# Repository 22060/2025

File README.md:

git clone https://github.com/22060/2025 --recursive

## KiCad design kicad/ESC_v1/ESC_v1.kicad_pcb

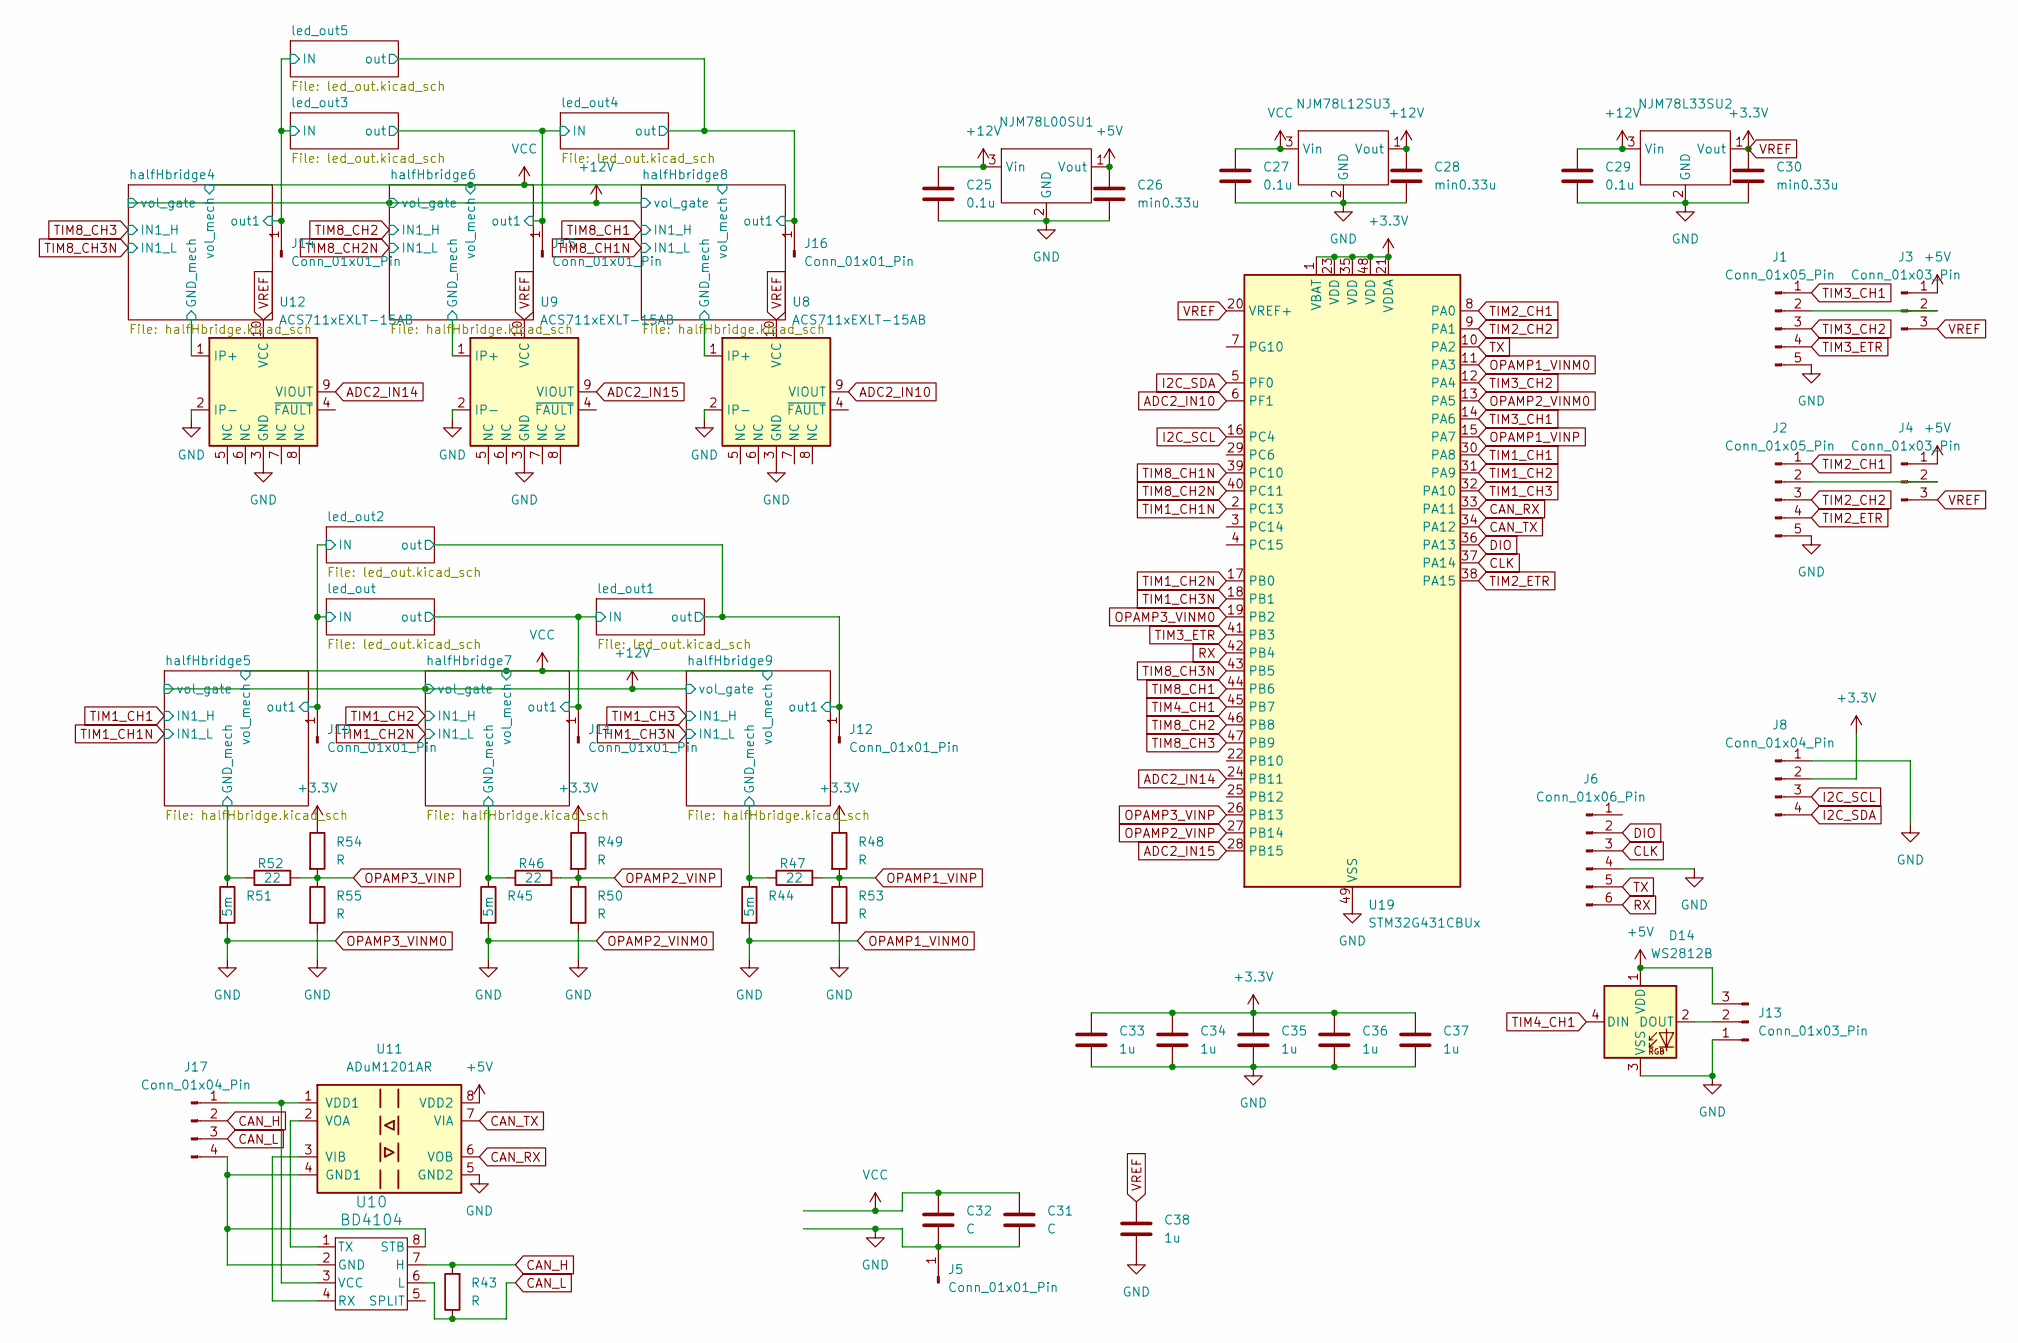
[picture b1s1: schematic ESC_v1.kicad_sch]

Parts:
C25, C27, C29: 0.1u; C_0603_1608Metric
C26, C28, C30: min0.33u; C_0603_1608Metric
C31, C32: C; C_Elec_10x10.2
C33, C34, C35, C36, C37, C38: 1u; C_0603_1608Metric
D14: WS2812B; LED_WS2812B_PLCC4_5.0x5.0mm_P3.2mm
J1, J2: Conn_01x05_Pin; JST_XH_S5B-XH-A_1x05_P2.50mm_Horizontal
J3, J4: Conn_01x03_Pin; PinSocket_1x03_P2.54mm_Vertical
J5: Conn_01x01_Pin; SolderWire-0.75sqmm_1x01_D1.25mm_OD2.3mm
J6: Conn_01x06_Pin; JST_ZH_B6B-ZR_1x06_P1.50mm_Vertical
J8: Conn_01x04_Pin; PinSocket_1x04_P2.54mm_Vertical
J10, J11, J12, J14, J15, J16: Conn_01x01_Pin; TestPoint_Pad_3.0x3.0mm
J13: Conn_01x03_Pin; Molex_KK-254_AE-6410-03A_1x03_P2.54mm_Vertical
J17: Conn_01x04_Pin; JST_PH_S4B-PH-K_1x04_P2.00mm_Horizontal
NJM78L00SU1, NJM78L12SU3, NJM78L33SU2: SOT-89-3
R43, R48, R49, R50, R53, R54, R55: R; R_0603_1608Metric_Pad0.98x0.95mm_HandSolder
R44, R45, R51: 5m; R_2010_5025Metric_Pad1.40x2.65mm_HandSolder
R46, R47, R52: 22; R_0603_1608Metric_Pad0.98x0.95mm_HandSolder
U8, U9, U12: ACS711xEXLT-15AB; Allegro_QFN-12-10-1EP_3x3mm_P0.5mm
U10: BD4104; SOP-J8
U11: ADuM1201AR; SOIC-8_3.9x4.9mm_P1.27mm
U19: STM32G431CBUx; QFN-48-1EP_7x7mm_P0.5mm_EP5.6x5.6mm

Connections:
+5V: C26.1, D14.1 (VDD), J3.1, J4.1, J13.3, NJM78L00SU1.1 (Vout), U11.8 (VDD2)
+12V: C25.1, C28.1, C29.1, NJM78L00SU1.3 (Vin), NJM78L12SU3.1 (Vout), NJM78L33SU2.3 (Vin); also elsewhere on the board
/halfHbridge4/GND_mech: U12.1 (IP+); also elsewhere on the board
/halfHbridge4/out1: J14.1; also elsewhere on the board
/halfHbridge5/GND_mech: R51.1, R52.1; also elsewhere on the board
/halfHbridge5/out1: J10.1; also elsewhere on the board
/halfHbridge6/GND_mech: U9.1 (IP+); also elsewhere on the board
/halfHbridge6/out1: J15.1; also elsewhere on the board
/halfHbridge7/GND_mech: R45.1, R46.1; also elsewhere on the board
/halfHbridge7/out1: J11.1; also elsewhere on the board
/halfHbridge8/GND_mech: U8.1 (IP+); also elsewhere on the board
/halfHbridge8/out1: J16.1; also elsewhere on the board
/halfHbridge9/GND_mech: R44.1, R47.1; also elsewhere on the board
/halfHbridge9/out1: J12.1; also elsewhere on the board
ADC2_IN10: U8.9 (VIOUT), U19.6 (PF1)
ADC2_IN14: U12.9 (VIOUT), U19.24 (PB11)
ADC2_IN15: U9.9 (VIOUT), U19.28 (PB15)
CAN_H: J17.2, R43.2, U10.7 (H)
CAN_L: J17.3, R43.1, U10.6 (L)
CAN_RX: U11.6 (VOB), U19.33 (PA11)
CAN_TX: U11.7 (VIA), U19.34 (PA12)
CLK: J6.3, U19.37 (PA14)
DIO: J6.2, U19.36 (PA13)
I2C_SCL: J8.3, U19.16 (PC4)
I2C_SDA: J8.4, U19.5 (PF0)
unnamed: D14.2 (DOUT), J13.2
unnamed: J1.2, J3.2
unnamed: J2.2, J4.2
unnamed: J17.1, U10.3 (VCC), U11.1 (VDD1)
unnamed: J17.4, U10.2 (GND), U10.8 (STB), U11.4 (GND1)
unnamed: U10.4 (RX), U11.3 (VIB)
unnamed: U10.1 (TX), U11.2 (VOA)
OPAMP1_VINM0: C25.2, C26.2, C27.2, C28.2, C29.2, C30.2, C31.2, C32.2, C33.2, C34.2, C35.2, C36.2, C37.2, C38.2, D14.3 (VSS), J1.5, J2.5, J5.1, J6.4, J8.1, J13.1, NJM78L00SU1.2 (GND), NJM78L12SU3.2 (GND), NJM78L33SU2.2 (GND), R44.2, R45.2, R50.2, R51.2, R53.2, R55.2, U8.2 (IP-), U8.3 (GND), U9.2 (IP-), U9.3 (GND), U11.5 (GND2), U12.2 (IP-), U12.3 (GND), U19.11 (PA3), U19.13 (PA5), U19.19 (PB2), U19.49 (VSS); also elsewhere on the board
OPAMP1_VINP: R47.2, R48.2, R53.1, U19.15 (PA7)
OPAMP2_VINP: R46.2, R49.2, R50.1, U19.27 (PB14)
OPAMP3_VINP: R52.2, R54.2, R55.1, U19.26 (PB13)
RX: J6.6, U19.42 (PB4)
TIM1_CH1: U19.30 (PA8); also elsewhere on the board
TIM1_CH1N: U19.2 (PC13); also elsewhere on the board
TIM1_CH2: U19.31 (PA9); also elsewhere on the board
TIM1_CH2N: U19.17 (PB0); also elsewhere on the board
TIM1_CH3: U19.32 (PA10); also elsewhere on the board
TIM1_CH3N: U19.18 (PB1); also elsewhere on the board
TIM2_CH1: J2.1, U19.8 (PA0)
TIM2_CH2: J2.3, U19.9 (PA1)
TIM2_ETR: J2.4, U19.38 (PA15)
TIM3_CH1: J1.1, U19.14 (PA6)
TIM3_CH2: J1.3, U19.12 (PA4)
TIM3_ETR: J1.4, U19.41 (PB3)
TIM4_CH1: D14.4 (DIN), U19.45 (PB7)
TIM8_CH1: U19.44 (PB6); also elsewhere on the board
TIM8_CH1N: U19.39 (PC10); also elsewhere on the board
TIM8_CH2: U19.46 (PB8); also elsewhere on the board
TIM8_CH2N: U19.40 (PC11); also elsewhere on the board
TIM8_CH3: U19.47 (PB9); also elsewhere on the board
TIM8_CH3N: U19.43 (PB5); also elsewhere on the board
TX: J6.5, U19.10 (PA2)
VCC: C27.1, C31.1, C32.1, NJM78L12SU3.3 (Vin); also elsewhere on the board
VREF: C30.1, C33.1, C34.1, C35.1, C36.1, C37.1, C38.1, J3.3, J4.3, J8.2, NJM78L33SU2.1 (Vout), R48.1, R49.1, R54.1, U8.10 (VCC), U9.10 (VCC), U12.10 (VCC), U19.1 (VBAT), U19.20 (VREF+), U19.21 (VDDA), U19.23 (VDD), U19.35 (VDD), U19.48 (VDD)

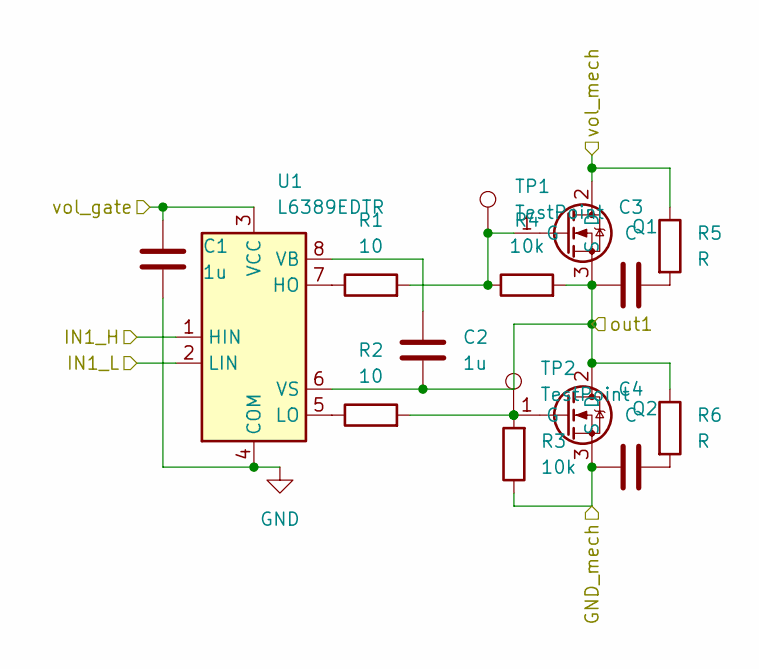
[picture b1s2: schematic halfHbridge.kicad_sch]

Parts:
C1, C2: 1u; C_0603_1608Metric
C3, C4: C; C_0603_1608Metric
Q1, Q2: RD3L07BBG
R1, R2: 10; R_0603_1608Metric_Pad0.98x0.95mm_HandSolder
R3, R4: 10k; R_0603_1608Metric_Pad0.98x0.95mm_HandSolder
R5, R6: R; R_0603_1608Metric_Pad0.98x0.95mm_HandSolder
TP1, TP2: TestPoint; TestPoint_THTPad_D1.5mm_Drill0.7mm
U1: L6389EDTR; SOIC-8_3.9x4.9mm_P1.27mm

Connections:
+12V: C1.1, U1.3 (VCC); also elsewhere on the board
/halfHbridge5/GND_mech: Q2.3 (S), R3.1; also elsewhere on the board
/halfHbridge5/out1: C2.2, Q1.3 (S), Q2.2 (D), R4.2, U1.6 (VS); also elsewhere on the board
unnamed: C3.2, R5.2
unnamed: C4.2, R6.2
unnamed: Q1.1 (G), R1.2, R4.1
unnamed: Q2.1 (G), R2.2, R3.2
unnamed: R1.1, U1.7 (HO)
unnamed: R2.1, U1.5 (LO)
unnamed: C2.1, U1.8 (VB)
OPAMP1_VINM0: C1.2, U1.4 (COM); also elsewhere on the board
TIM1_CH1: U1.1 (HIN); also elsewhere on the board
TIM1_CH1N: U1.2 (LIN); also elsewhere on the board
VCC: Q1.2 (D), R5.1; also elsewhere on the board

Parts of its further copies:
C5, C6, C9, C10, C11, C12, C17, C18, C21, C22: 1u; C_0603_1608Metric
Q3, Q4, Q5, Q6, Q7, Q8, Q9, Q10, Q11, Q12: RD3L07BBG
R7, R8, R13, R14, R15, R16, R25, R26, R31, R32: 10; R_0603_1608Metric_Pad0.98x0.95mm_HandSolder
R9, R10, R17, R18, R19, R20, R27, R28, R33, R34: 10k; R_0603_1608Metric_Pad0.98x0.95mm_HandSolder
U2, U3, U4, U5, U6: L6389EDTR; SOIC-8_3.9x4.9mm_P1.27mm

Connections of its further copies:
+12V: C5.1, C9.1, C10.1, C17.1, C21.1, U2.3 (VCC), U3.3 (VCC), U4.3 (VCC), U5.3 (VCC), U6.3 (VCC); also elsewhere on the board
/halfHbridge4/GND_mech: Q4.3 (S), R9.1; also elsewhere on the board
/halfHbridge4/out1: C6.2, Q3.3 (S), Q4.2 (D), R10.2, U2.6 (VS); also elsewhere on the board
/halfHbridge6/GND_mech: Q8.3 (S), R18.1; also elsewhere on the board
/halfHbridge6/out1: C12.2, Q7.3 (S), Q8.2 (D), R20.2, U4.6 (VS); also elsewhere on the board
/halfHbridge7/GND_mech: Q6.3 (S), R17.1; also elsewhere on the board
/halfHbridge7/out1: C11.2, Q5.3 (S), Q6.2 (D), R19.2, U3.6 (VS); also elsewhere on the board
/halfHbridge8/GND_mech: Q10.3 (S), R27.1; also elsewhere on the board
/halfHbridge8/out1: C18.2, Q9.3 (S), Q10.2 (D), R28.2, U5.6 (VS); also elsewhere on the board
/halfHbridge9/GND_mech: Q12.3 (S), R33.1; also elsewhere on the board
/halfHbridge9/out1: C22.2, Q11.3 (S), Q12.2 (D), R34.2, U6.6 (VS); also elsewhere on the board
unnamed: Q3.1 (G), R7.2, R10.1
unnamed: Q4.1 (G), R8.2, R9.2
unnamed: Q5.1 (G), R13.2, R19.1
unnamed: Q6.1 (G), R14.2, R17.2
unnamed: Q7.1 (G), R15.2, R20.1
unnamed: Q8.1 (G), R16.2, R18.2
unnamed: Q9.1 (G), R25.2, R28.1
unnamed: Q10.1 (G), R26.2, R27.2
unnamed: Q11.1 (G), R31.2, R34.1
unnamed: Q12.1 (G), R32.2, R33.2
unnamed: R7.1, U2.7 (HO)
unnamed: R8.1, U2.5 (LO)
unnamed: C6.1, U2.8 (VB)
unnamed: R13.1, U3.7 (HO)
unnamed: R14.1, U3.5 (LO)
unnamed: C11.1, U3.8 (VB)
unnamed: R15.1, U4.7 (HO)
unnamed: R16.1, U4.5 (LO)
unnamed: C12.1, U4.8 (VB)
unnamed: R25.1, U5.7 (HO)
unnamed: R26.1, U5.5 (LO)
unnamed: C18.1, U5.8 (VB)
unnamed: R31.1, U6.7 (HO)
unnamed: R32.1, U6.5 (LO)
unnamed: C22.1, U6.8 (VB)
OPAMP1_VINM0: C5.2, C9.2, C10.2, C17.2, C21.2, U2.4 (COM), U3.4 (COM), U4.4 (COM), U5.4 (COM), U6.4 (COM); also elsewhere on the board
TIM1_CH2: U3.1 (HIN); also elsewhere on the board
TIM1_CH2N: U3.2 (LIN); also elsewhere on the board
TIM1_CH3: U6.1 (HIN); also elsewhere on the board
TIM1_CH3N: U6.2 (LIN); also elsewhere on the board
TIM8_CH1: U5.1 (HIN); also elsewhere on the board
TIM8_CH1N: U5.2 (LIN); also elsewhere on the board
TIM8_CH2: U4.1 (HIN); also elsewhere on the board
TIM8_CH2N: U4.2 (LIN); also elsewhere on the board
TIM8_CH3: U2.1 (HIN); also elsewhere on the board
TIM8_CH3N: U2.2 (LIN); also elsewhere on the board
VCC: Q3.2 (D), Q5.2 (D), Q7.2 (D), Q9.2 (D), Q11.2 (D); also elsewhere on the board

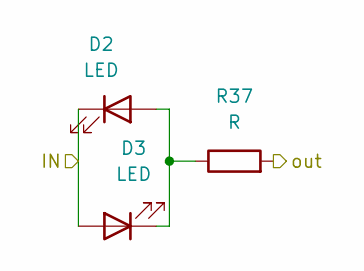
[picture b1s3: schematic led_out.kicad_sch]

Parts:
D2, D3: LED; LED_0603_1608Metric
R37: R; R_0603_1608Metric_Pad0.98x0.95mm_HandSolder

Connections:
/halfHbridge5/out1: D2.1 (K), D3.2 (A); also elsewhere on the board
/halfHbridge7/out1: R37.2; also elsewhere on the board
unnamed: D2.2 (A), D3.1 (K), R37.1

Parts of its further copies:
D1, D4, D5, D6, D7, D8, D9, D10, D11, D12: LED; LED_0603_1608Metric
R38, R39, R40, R41, R42: R; R_0603_1608Metric_Pad0.98x0.95mm_HandSolder

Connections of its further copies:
/halfHbridge4/out1: D1.1 (K), D8.2 (A), D11.1 (K), D12.2 (A); also elsewhere on the board
/halfHbridge5/out1: D6.1 (K), D7.2 (A); also elsewhere on the board
/halfHbridge6/out1: D9.1 (K), D10.2 (A), R40.2; also elsewhere on the board
/halfHbridge7/out1: D4.1 (K), D5.2 (A); also elsewhere on the board
/halfHbridge8/out1: R41.2, R42.2; also elsewhere on the board
/halfHbridge9/out1: R38.2, R39.2; also elsewhere on the board
unnamed: D1.2 (A), D8.1 (K), R40.1
unnamed: D4.2 (A), D5.1 (K), R38.1
unnamed: D6.2 (A), D7.1 (K), R39.1
unnamed: D9.2 (A), D10.1 (K), R41.1
unnamed: D11.2 (A), D12.1 (K), R42.1

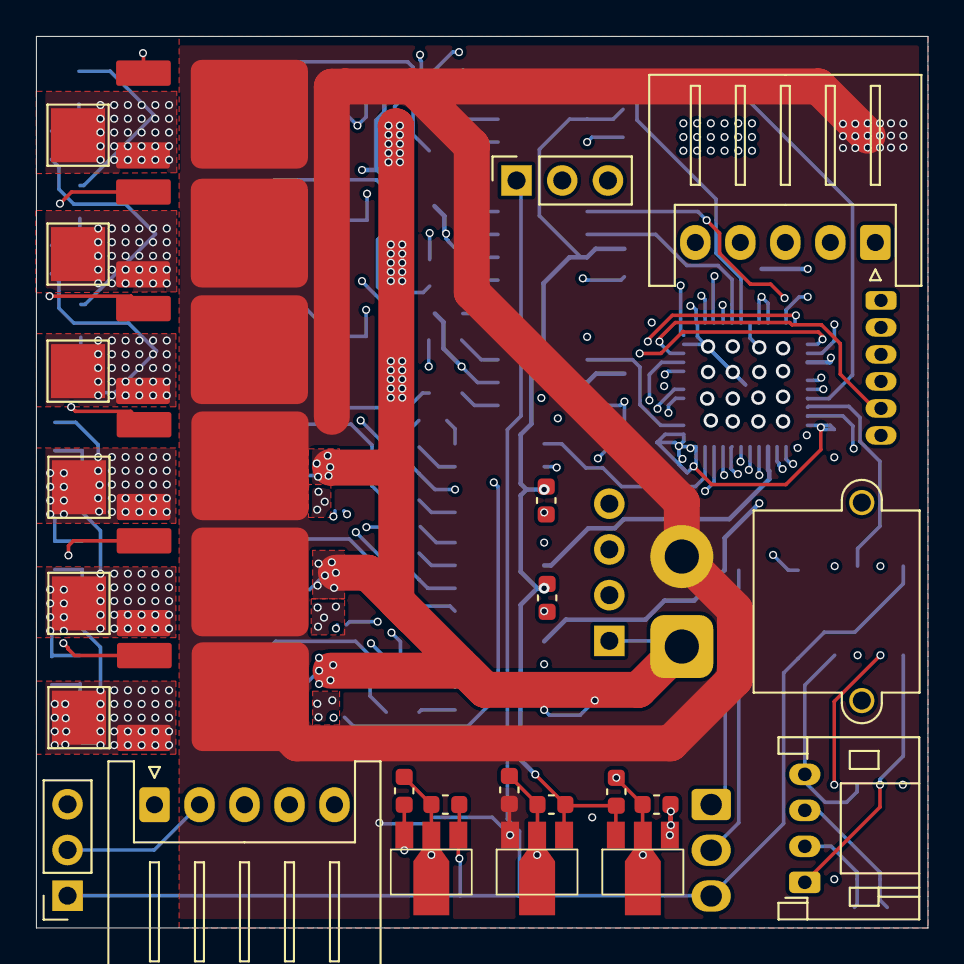
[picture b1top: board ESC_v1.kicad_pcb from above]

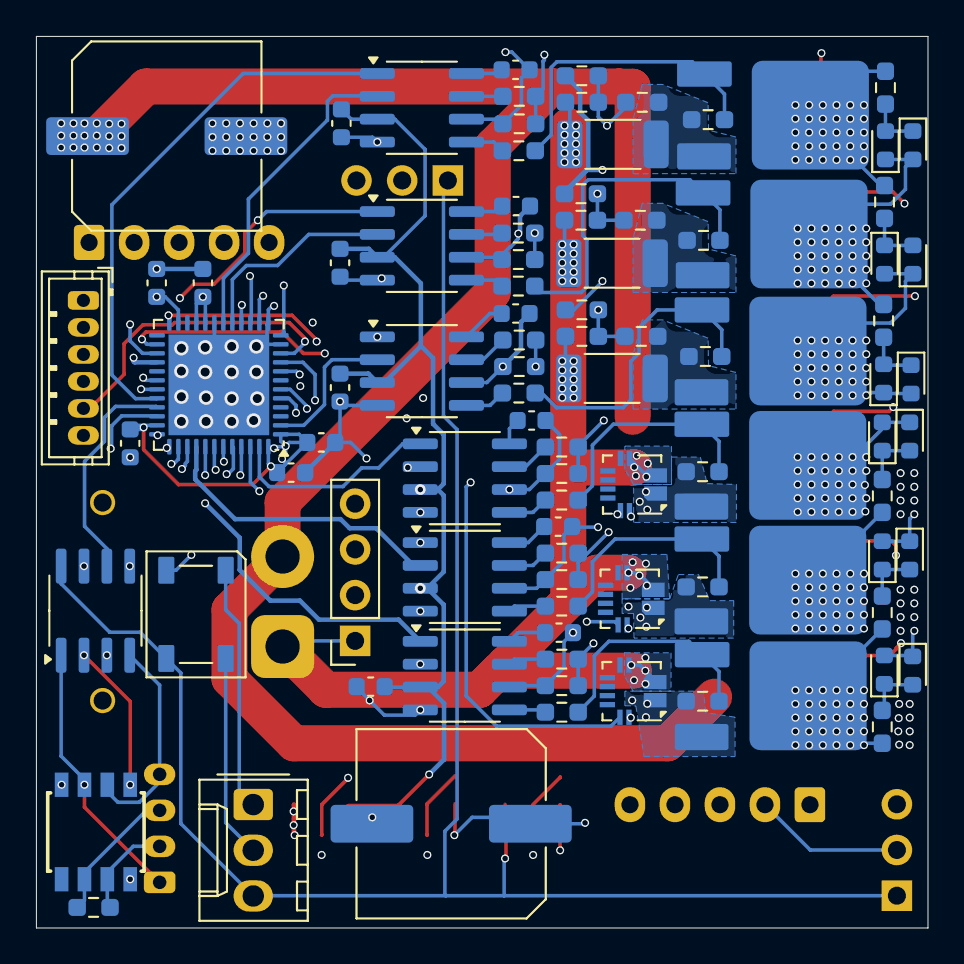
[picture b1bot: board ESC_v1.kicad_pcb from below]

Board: 4 copper layers, 49.5 x 49.5 mm, 123 parts (94 on the bottom side), 95 nets.

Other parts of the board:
J9: Conn_01x02_Pin; AMASS_XT30PW-M_1x02_P2.50mm_Horizontal

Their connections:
OPAMP1_VINM0: J9.1; also elsewhere on the board
VCC: J9.2; also elsewhere on the board

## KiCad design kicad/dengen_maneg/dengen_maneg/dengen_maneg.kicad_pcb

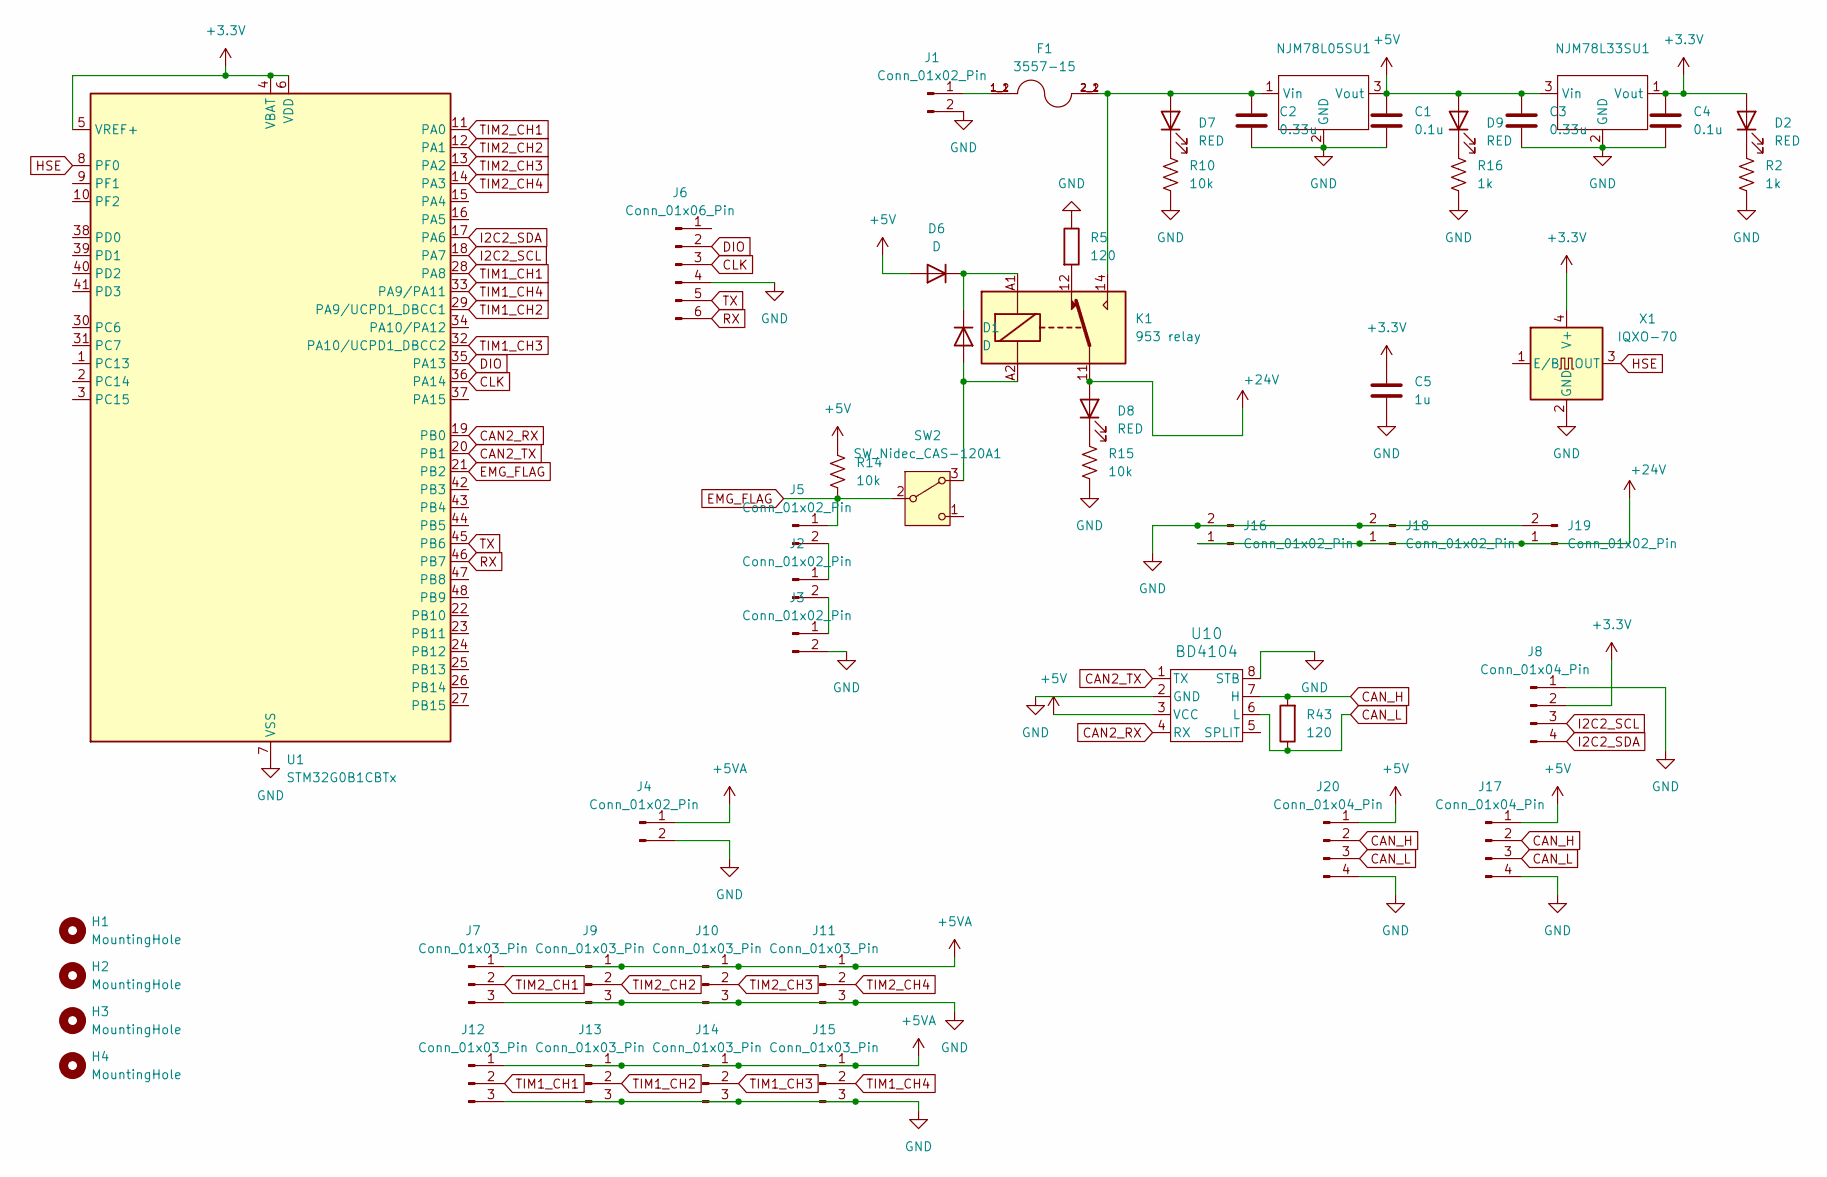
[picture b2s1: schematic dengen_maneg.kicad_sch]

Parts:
C1, C4: 0.1u; C_0603_1608Metric
C2, C3: 0.33u; C_0603_1608Metric
C5: 1u; C_0603_1608Metric
D1, D6: D; D_MicroSMP_AK
D2, D7, D8, D9: RED; LED_0603_1608Metric_Pad1.05x0.95mm_HandSolder
F1: 3557-15; PARTREV D
H1, H2, H3, H4: MountingHole; MountingHole_3.2mm_M3
J1: Conn_01x02_Pin; AMASS_XT60PW-M_1x02_P7.20mm_Horizontal
J2, J3, J5: Conn_01x02_Pin; JST_XH_S2B-XH-A_1x02_P2.50mm_Horizontal
J4: Conn_01x02_Pin; JST_XH_B2B-XH-A_1x02_P2.50mm_Vertical
J6: Conn_01x06_Pin; JST_ZH_B6B-ZR_1x06_P1.50mm_Vertical
J7, J9, J10, J11, J12, J13, J14, J15: Conn_01x03_Pin; JST_XH_B3B-XH-A_1x03_P2.50mm_Vertical
J8: Conn_01x04_Pin; PinSocket_1x04_P2.54mm_Vertical
J16, J18, J19: Conn_01x02_Pin; AMASS_XT30UPB-F_1x02_P5.0mm_Vertical
J17, J20: Conn_01x04_Pin; JST_PH_S4B-PH-K_1x04_P2.00mm_Horizontal
K1: 953 relay
NJM78L05SU1: TO-252-2
NJM78L33SU1: SOT-89-3
R2, R16: 1k; R_0603_1608Metric_Pad0.98x0.95mm_HandSolder
R5: 120; R_Axial_DIN0617_L17.0mm_D6.0mm_P5.08mm_Vertical
R10, R14, R15: 10k; R_0603_1608Metric_Pad0.98x0.95mm_HandSolder
R43: 120; R_0603_1608Metric_Pad0.98x0.95mm_HandSolder
SW2: SW_Nidec_CAS-120A1; JST_XH_B3B-XH-A_1x03_P2.50mm_Vertical
U1: STM32G0B1CBTx; LQFP-48_7x7mm_P0.5mm
U10: BD4104; SOP-J8
X1: IQXO-70; Oscillator_SMD_IQD_IQXO70-4Pin_7.5x5.0mm

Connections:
+3.3V: C4.1, C5.1, D2.2 (A), J8.2, NJM78L33SU1.1 (Vout), U1.4 (VBAT), U1.5 (VREF+), U1.6 (VDD), X1.4 (V+)
+5V: C1.1, C3.1, D6.2 (A), D9.2 (A), J17.1, J20.1, NJM78L05SU1.3 (Vout), NJM78L33SU1.3 (Vin), R14.2, U10.3 (VCC)
+5VA: J4.1, J7.1, J9.1, J10.1, J11.1, J12.1, J13.1, J14.1, J15.1
+24V: D8.2 (A), J16.1, J18.1, J19.1, K1.11
CAN2_RX: U1.19 (PB0), U10.4 (RX)
CAN2_TX: U1.20 (PB1), U10.1 (TX)
CAN_H: J17.2, J20.2, R43.2, U10.7 (H)
CAN_L: J17.3, J20.3, R43.1, U10.6 (L)
CLK: J6.3, U1.36 (PA14)
DIO: J6.2, U1.35 (PA13)
EMG_FLAG: J5.1, R14.1, SW2.2 (B), U1.21 (PB2)
GND: C1.2, C2.2, C3.2, C4.2, C5.2, J1.2, J3.2, J4.2, J6.4, J7.3, J8.1, J9.3, J10.3, J11.3, J12.3, J13.3, J14.3, J15.3, J16.2, J17.4, J18.2, J19.2, J20.4, NJM78L05SU1.2 (GND), NJM78L33SU1.2 (GND), R2.2, R5.1, R10.2, R15.2, R16.2, U1.7 (VSS), U10.2 (GND), U10.8 (STB), X1.2 (GND)
HSE: U1.8 (PF0), X1.3 (OUT)
I2C2_SCL: J8.3, U1.18 (PA7)
I2C2_SDA: J8.4, U1.17 (PA6)
unnamed: D1.2 (A), K1.A2, SW2.3 (A)
unnamed: D1.1 (K), D6.1 (K), K1.A1
unnamed: D2.1 (K), R2.1
unnamed: C2.1, D7.2 (A), F1.2_1, F1.2_2, K1.14, NJM78L05SU1.1 (Vin)
unnamed: D7.1 (K), R10.1
unnamed: D8.1 (K), R15.1
unnamed: D9.1 (K), R16.1
unnamed: F1.1_1, F1.1_2, J1.1
unnamed: J2.1, J5.2
unnamed: J2.2, J3.1
unnamed: K1.12, R5.2
RX: J6.6, U1.46 (PB7)
TIM1_CH1: J12.2, U1.28 (PA8)
TIM1_CH2: J13.2, U1.29 (PA9/UCPD1_DBCC1)
TIM1_CH3: J14.2, U1.32 (PA10/UCPD1_DBCC2)
TIM1_CH4: J15.2, U1.33 (PA9/PA11)
TIM2_CH1: J7.2, U1.11 (PA0)
TIM2_CH2: J9.2, U1.12 (PA1)
TIM2_CH3: J10.2, U1.13 (PA2)
TIM2_CH4: J11.2, U1.14 (PA3)
TX: J6.5, U1.45 (PB6)

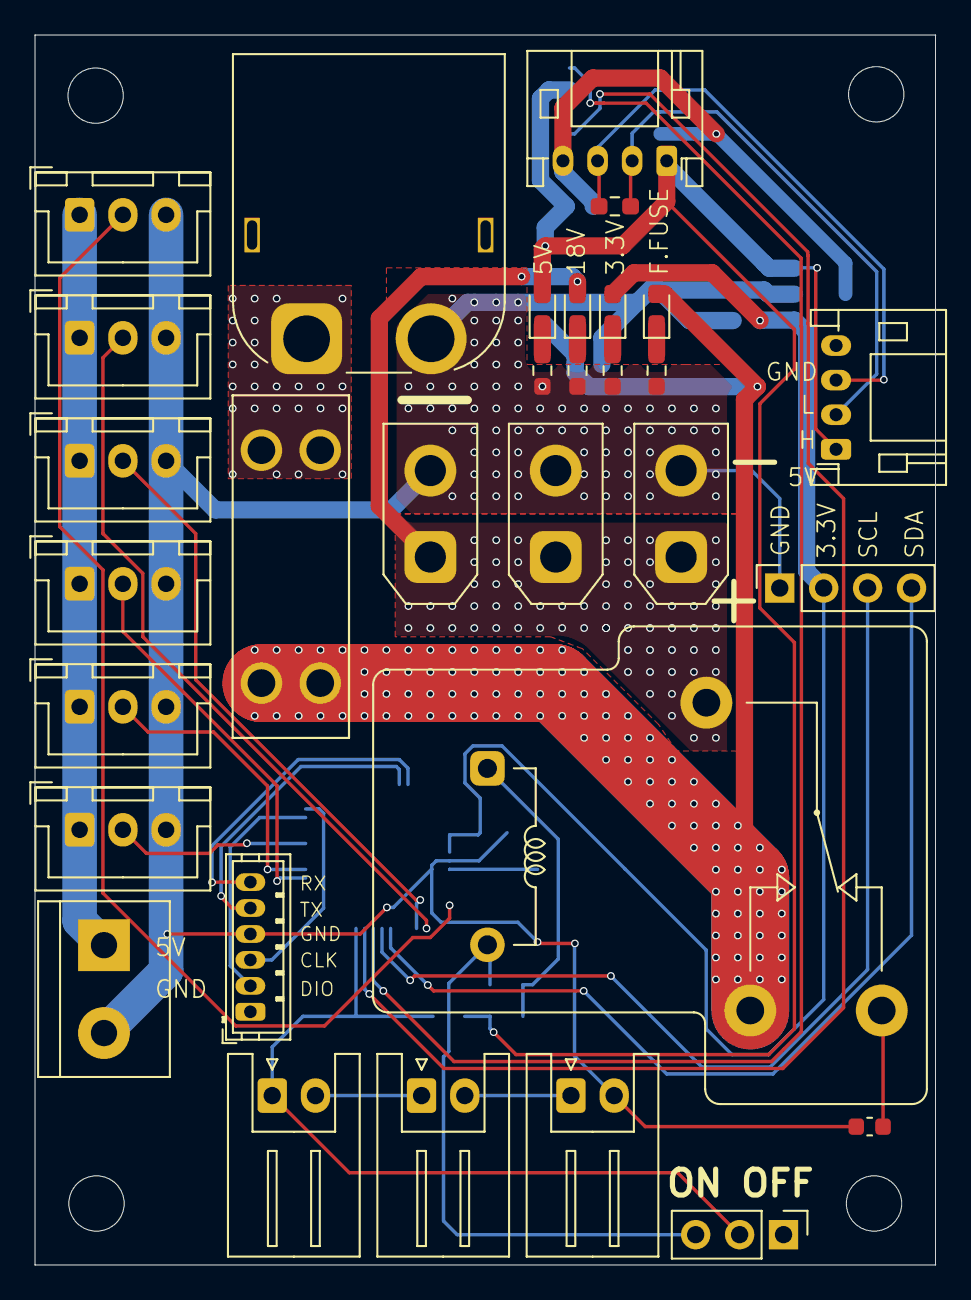
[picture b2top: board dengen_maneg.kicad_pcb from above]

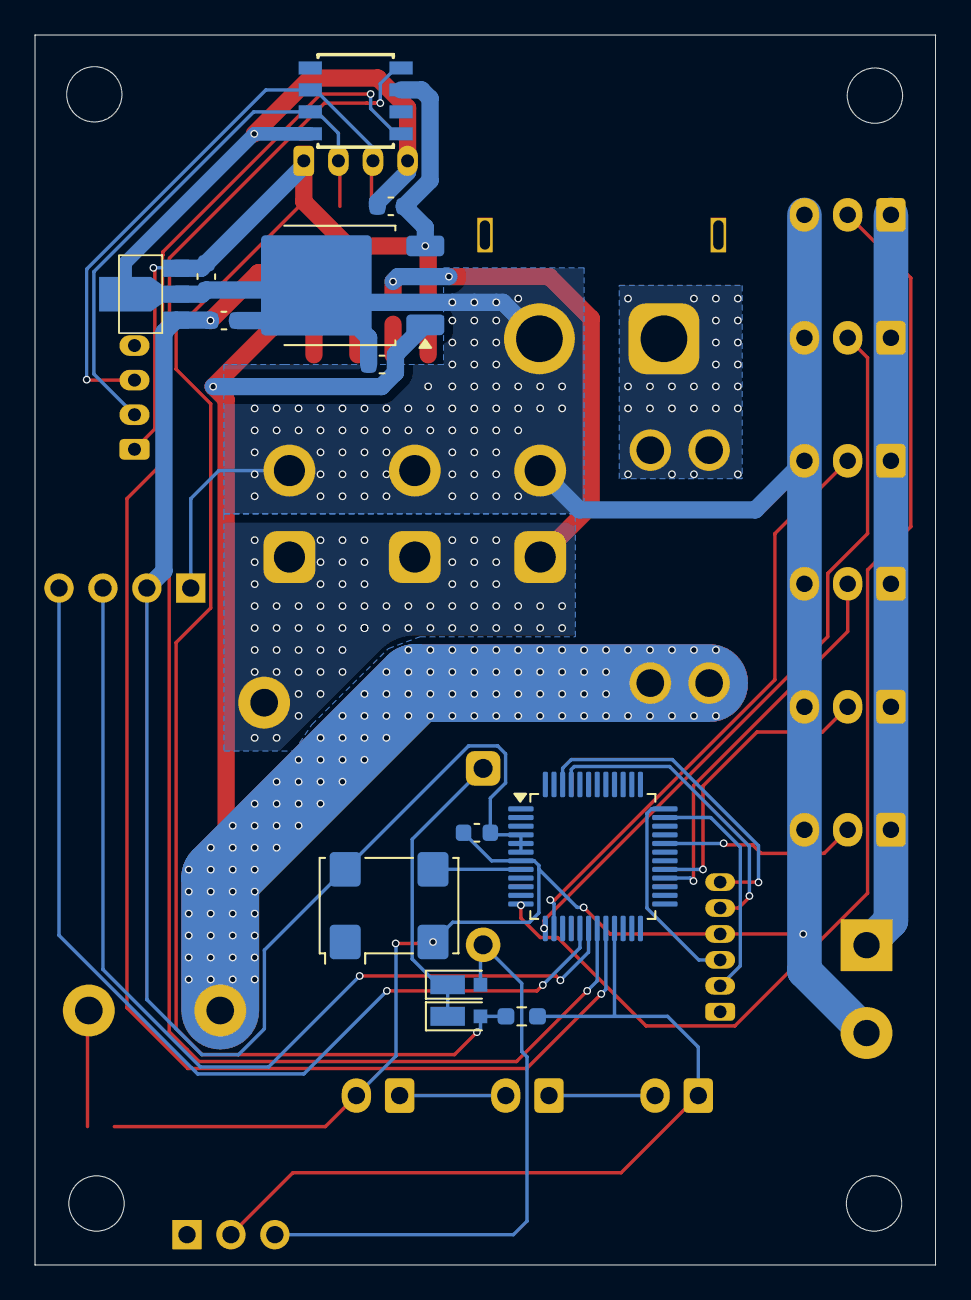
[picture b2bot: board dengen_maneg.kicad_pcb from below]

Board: 2 copper layers, 52.1 x 71.1 mm, 48 parts (13 on the bottom side), 34 nets.
